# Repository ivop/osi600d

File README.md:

# Ohio Scientific 600D Remake

### Remake of the Ohio Scientific 600D PCB

* The new [schematics](doc/osi600d-schematic.pdf) are based on the original schematics, but with all [errors](doc/errors.txt) fixed.
* The PCB is mostly identical to the original, but with added silkscreen, and jumpers instead of trace cuts.
* In theory, you can build it solely with the [BOM](doc/osi600d-bom.pdf) and the new silkscreen, but the original Assembly Instructions still apply 100%.
* PCB uses Cherry MX key switches.
* 4-pin or 5-pin headers for USB-C or Micro USB breakout boards for power supply (e.g. Raspberry Pi 3A PS).
* Use [ramtest2114](https://github.com/ivop/ramtest2114) to test RAM chips acquired from Ali.

Can be paired with the [Ohio Scientific 610B Floppy Controller and Memory Expansion](https://github.com/ivop/osi610b).

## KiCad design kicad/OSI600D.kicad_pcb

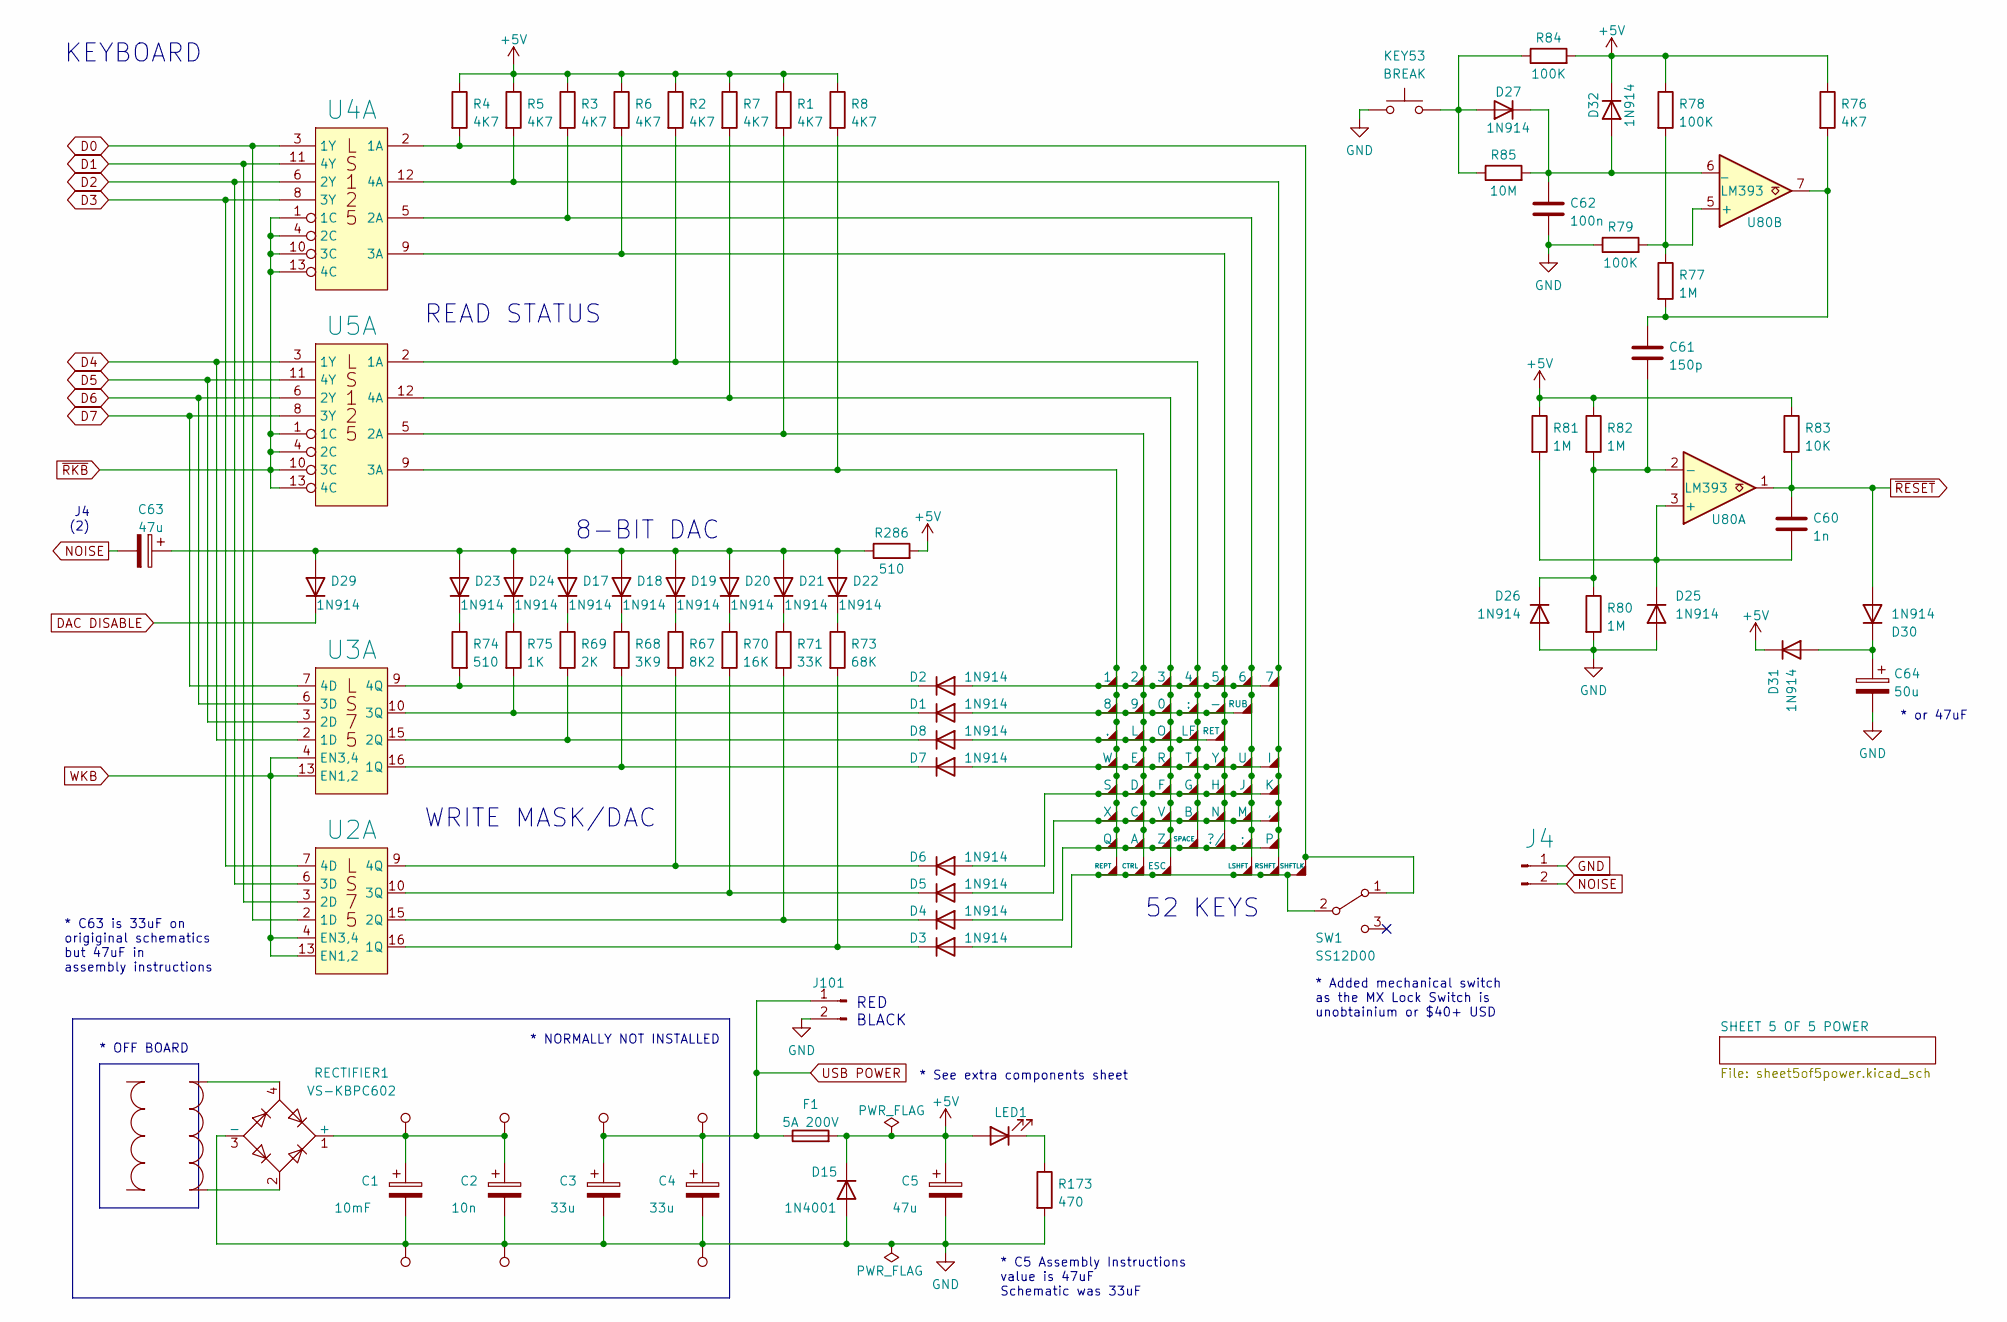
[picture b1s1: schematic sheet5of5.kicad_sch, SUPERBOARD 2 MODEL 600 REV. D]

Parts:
C1: 10mF; C_Radial_D10.0mm_H16.0mm_P5.00mm
C2: 10n; CP_Axial_L10.0mm_D4.5mm_P15.00mm_Horizontal
C3, C4: 33u; CP_Axial_L10.0mm_D4.5mm_P15.00mm_Horizontal
C5: 47u; CP_Axial_L10.0mm_D4.5mm_P15.00mm_Horizontal
C60: 1n; C_Disc_D7.5mm_W2.5mm_P7.50mm
C61: 150p; C_Disc_D7.5mm_W2.5mm_P7.50mm
C62: 100n; C_Disc_D7.5mm_W2.5mm_P7.50mm
C63: 47u; CP_Axial_L11.0mm_D5.0mm_P18.00mm_Horizontal
C64: 50u; CP_Axial_L11.0mm_D5.0mm_P18.00mm_Horizontal
D1, D2, D3, D4, D5, D6, D7, D8, D17, D18, D19, D20, D21, D22, D23, D24, D25, D26, D27, D29, D30, D31, D32: 1N914; D_DO-35_SOD27_P10.16mm_Horizontal
D15: 1N4001; D_DO-41_SOD81_P12.70mm_Horizontal
F1: 5A 200V; Fuse Holder
J4, J101: Conn_01x02_Male; Molex_KK-396_A-41791-0002_1x02_P3.96mm_Vertical
KEY1: 1; SW_Cherry_MX_PCB_1.00u
KEY2: 8; SW_Cherry_MX_PCB_1.00u
KEY3: .; SW_Cherry_MX_PCB_1.00u
KEY4: W; SW_Cherry_MX_PCB_1.00u
KEY5: S; SW_Cherry_MX_PCB_1.00u
KEY6: X; SW_Cherry_MX_PCB_1.00u
KEY7: Q; SW_Cherry_MX_PCB_1.00u
KEY8: REPT; SW_Cherry_MX_PCB_1.00u
KEY9: 2; SW_Cherry_MX_PCB_1.00u
KEY10: 9; SW_Cherry_MX_PCB_1.00u
KEY11: L; SW_Cherry_MX_PCB_1.00u
KEY12: E; SW_Cherry_MX_PCB_1.00u
KEY13: D; SW_Cherry_MX_PCB_1.00u
KEY14: C; SW_Cherry_MX_PCB_1.00u
KEY15: A; SW_Cherry_MX_PCB_1.00u
KEY16: CTRL; SW_Cherry_MX_PCB_1.00u
KEY17: 3; SW_Cherry_MX_PCB_1.00u
KEY18: 0; SW_Cherry_MX_PCB_1.00u
KEY19: O; SW_Cherry_MX_PCB_1.00u
KEY20: R; SW_Cherry_MX_PCB_1.00u
KEY21: F; SW_Cherry_MX_PCB_1.00u
KEY22: V; SW_Cherry_MX_PCB_1.00u
KEY23: Z; SW_Cherry_MX_PCB_1.00u
KEY24: ESC; SW_Cherry_MX_PCB_1.00u
KEY25: 4; SW_Cherry_MX_PCB_1.00u
KEY26: :; SW_Cherry_MX_PCB_1.00u
KEY27: LF; SW_Cherry_MX_PCB_1.00u
KEY28: T; SW_Cherry_MX_PCB_1.00u
KEY29: G; SW_Cherry_MX_PCB_1.00u
KEY30: B; SW_Cherry_MX_PCB_1.00u
KEY31: SPACE; SW_Cherry_MX_PCB_1.00u
KEY32: 5; SW_Cherry_MX_PCB_1.00u
KEY33: -; SW_Cherry_MX_PCB_1.00u
KEY34: RET; SW_Cherry_MX_PCB_1.50u
KEY35: Y; SW_Cherry_MX_PCB_1.00u
KEY36: H; SW_Cherry_MX_PCB_1.00u
KEY37: N; SW_Cherry_MX_PCB_1.00u
KEY38: ?/; SW_Cherry_MX_PCB_1.00u
KEY39: 6; SW_Cherry_MX_PCB_1.00u
KEY40: RUB; SW_Cherry_MX_PCB_1.00u
KEY41: U; SW_Cherry_MX_PCB_1.00u
KEY42: J; SW_Cherry_MX_PCB_1.00u
KEY43: M; SW_Cherry_MX_PCB_1.00u
KEY44: ;; SW_Cherry_MX_PCB_1.00u
KEY45: LSHFT; SW_Cherry_MX_PCB_1.50u
KEY46: 7; SW_Cherry_MX_PCB_1.00u
KEY47: I; SW_Cherry_MX_PCB_1.00u
KEY48: K; SW_Cherry_MX_PCB_1.00u
KEY49: ,; SW_Cherry_MX_PCB_1.00u
KEY50: P; SW_Cherry_MX_PCB_1.00u
KEY51: RSHFT; SW_Cherry_MX_PCB_1.50u
KEY52: SHFTLK; SW_Cherry_MX_PCB_1.00u
KEY53: BREAK; SW_Cherry_MX_PCB_1.00u
LED1: LED; LED_D5.0mm
PIN8, PIN9, PIN10, PIN11, PIN12, PIN13, PIN14: JUMPER_PIN; PinHeader_1x01_P2.54mm_Vertical
R1, R2, R3, R4, R5, R6, R7, R8: 4K7; R_Axial_DIN0207_L6.3mm_D2.5mm_P2.54mm_Vertical
R67: 8K2; R_Axial_DIN0207_L6.3mm_D2.5mm_P2.54mm_Vertical
R68: 3K9; R_Axial_DIN0207_L6.3mm_D2.5mm_P2.54mm_Vertical
R69: 2K; R_Axial_DIN0207_L6.3mm_D2.5mm_P2.54mm_Vertical
R70: 16K; R_Axial_DIN0207_L6.3mm_D2.5mm_P2.54mm_Vertical
R71: 33K; R_Axial_DIN0207_L6.3mm_D2.5mm_P2.54mm_Vertical
R73: 68K; R_Axial_DIN0207_L6.3mm_D2.5mm_P2.54mm_Vertical
R74: 510; R_Axial_DIN0207_L6.3mm_D2.5mm_P2.54mm_Vertical
R75: 1K; R_Axial_DIN0207_L6.3mm_D2.5mm_P2.54mm_Vertical
R76: 4K7; R_Axial_DIN0207_500mils_Horizontal
R77, R80, R81, R82: 1M; R_Axial_DIN0207_500mils_Horizontal
R78, R79, R84: 100K; R_Axial_DIN0207_500mils_Horizontal
R83: 10K; R_Axial_DIN0207_500mils_Horizontal
R85: 10M; R_Axial_DIN0207_500mils_Horizontal
R173: 470; R_Axial_DIN0207_L6.3mm_D2.5mm_P2.54mm_Vertical
R286: 510; R_Axial_DIN0207_500mils_Horizontal
RECTIFIER1: VS-KBPC602; Diode_Bridge_Vishay_KBPC6
SW1: SS12D00
TRANSFORMER1: TRANSFORMER_(OFF_BOARD); Molex_KK-396_A-41791-0002_1x02_P3.96mm_Vertical
U2, U3: LS75; DIP-16_W7.62mm_Socket_LongPads
U4, U5: LS125; DIP-14_W7.62mm_Socket_LongPads
U80: LM393; DIP-8_W7.62mm_Socket_LongPads

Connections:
+5V: C5.1, D15.1 (K), D31.1 (K), D32.1 (K), F1.2, LED1.2 (A), R1.1, R2.1, R3.1, R4.1, R5.1, R6.1, R7.1, R8.1, R76.1, R78.1, R81.1, R82.1, R83.1, R84.2, R286.2; also elsewhere on the board
D0: U2.2 (1D), U4.3 (1Y); also elsewhere on the board
D1: U2.3 (2D), U4.11 (4Y); also elsewhere on the board
D2: U2.6 (3D), U4.6 (2Y); also elsewhere on the board
D3: U2.7 (4D), U4.8 (3Y); also elsewhere on the board
D4: U3.2 (1D), U5.3 (1Y); also elsewhere on the board
D5: U3.3 (2D), U5.11 (4Y); also elsewhere on the board
D6: U3.6 (3D), U5.6 (2Y); also elsewhere on the board
D7: U3.7 (4D), U5.8 (3Y); also elsewhere on the board
DAC DISABLE: D29.1 (K); also elsewhere on the board
GND: C1.2, C2.2, C3.2, C4.2, C5.2, C62.2, C64.2, D15.2 (A), D25.2 (A), D26.2 (A), J4.1, J101.2, KEY53.2, PIN9.1, PIN11.1, PIN14.1, R79.1, R80.2, R173.2, RECTIFIER1.3 (-); also elsewhere on the board
NOISE: C63.2, J4.2
unnamed: C1.1, C2.1, PIN8.1, PIN10.1, RECTIFIER1.1 (+)
unnamed: C60.2, D25.1 (K), R81.2, U80.3 (+)
unnamed: C61.1, R76.2, R77.2, U80.7
unnamed: C61.2, D26.1 (K), R80.1, R82.2, U80.2 (-)
unnamed: C62.1, D27.1 (K), D32.2 (A), R85.2, U80.6 (_)
unnamed: C63.1, D17.2 (A), D18.2 (A), D19.2 (A), D20.2 (A), D21.2 (A), D22.2 (A), D23.2 (A), D24.2 (A), D29.2 (A), R286.1
unnamed: C64.1, D30.1 (K), D31.2 (A)
unnamed: D1.1 (K), R75.2, U3.10 (3Q), U3.14 (~2Q)
unnamed: D1.2 (A), KEY2.1, KEY10.1, KEY18.1, KEY26.1, KEY33.1, KEY40.1
unnamed: D2.1 (K), R74.2, U3.9 (4Q)
unnamed: D2.2 (A), KEY1.1, KEY9.1, KEY17.1, KEY25.1, KEY32.1, KEY39.1, KEY46.1
unnamed: D3.1 (K), R73.2, U2.16 (1Q)
unnamed: D3.2 (A), KEY8.1, KEY16.1, KEY24.1, KEY45.1, KEY51.1, KEY52.1, SW1.2 (B)
unnamed: D4.1 (K), R71.2, U2.15 (2Q)
unnamed: D4.2 (A), KEY7.1, KEY15.1, KEY23.1, KEY31.1, KEY38.1, KEY44.1, KEY50.1
unnamed: D5.1 (K), R70.2, U2.10 (3Q)
unnamed: D5.2 (A), KEY6.1, KEY14.1, KEY22.1, KEY30.1, KEY37.1, KEY43.1, KEY49.1
unnamed: D6.1 (K), R67.2, U2.9 (4Q)
unnamed: D6.2 (A), KEY5.1, KEY13.1, KEY21.1, KEY29.1, KEY36.1, KEY42.1, KEY48.1
unnamed: D7.1 (K), R68.2, U3.16 (1Q)
unnamed: D7.2 (A), KEY4.1, KEY12.1, KEY20.1, KEY28.1, KEY35.1, KEY41.1, KEY47.1
unnamed: D8.1 (K), R69.2, U3.15 (2Q)
unnamed: D8.2 (A), KEY3.1, KEY11.1, KEY19.1, KEY27.1, KEY34.1
unnamed: D17.1 (K), R69.1
unnamed: D18.1 (K), R68.1
unnamed: D19.1 (K), R67.1
unnamed: D20.1 (K), R70.1
unnamed: D21.1 (K), R71.1
unnamed: D22.1 (K), R73.1
unnamed: D23.1 (K), R74.1
unnamed: D24.1 (K), R75.1
unnamed: D27.2 (A), KEY53.1, R84.1, R85.1
unnamed: KEY1.2, KEY2.2, KEY3.2, KEY4.2, KEY5.2, KEY6.2, KEY7.2, KEY8.2, R8.2, U5.9 (3A)
unnamed: KEY9.2, KEY10.2, KEY11.2, KEY12.2, KEY13.2, KEY14.2, KEY15.2, KEY16.2, R1.2, U5.5 (2A)
unnamed: KEY17.2, KEY18.2, KEY19.2, KEY20.2, KEY21.2, KEY22.2, KEY23.2, KEY24.2, R7.2, U5.12 (4A)
unnamed: KEY25.2, KEY26.2, KEY27.2, KEY28.2, KEY29.2, KEY30.2, KEY31.2, R2.2, U5.2 (1A)
unnamed: KEY32.2, KEY33.2, KEY34.2, KEY35.2, KEY36.2, KEY37.2, KEY38.2, R6.2, U4.9 (3A)
unnamed: KEY39.2, KEY40.2, KEY41.2, KEY42.2, KEY43.2, KEY44.2, KEY45.2, R3.2, U4.5 (2A)
unnamed: KEY46.2, KEY47.2, KEY48.2, KEY49.2, KEY50.2, KEY51.2, R5.2, U4.12 (4A)
unnamed: KEY52.2, R4.2, SW1.1 (A), U4.2 (1A)
unnamed: LED1.1 (K), R173.1
unnamed: R77.1, R78.2, R79.2, U80.5 (+)
unnamed 171: RECTIFIER1.2, TRANSFORMER1.2; also elsewhere on the board
unnamed: RECTIFIER1.4, TRANSFORMER1.1
USB POWER: C3.1, C4.1, F1.1, J101.1, PIN12.1, PIN13.1; also elsewhere on the board
WKB: U2.4 (EN3,4), U2.13 (EN1,2), U3.4 (EN3,4), U3.13 (EN1,2); also elsewhere on the board
~RESET: C60.1, D30.2 (A), R83.2, U80.1; also elsewhere on the board
~RKB: U4.1 (1C), U4.4 (2C), U4.10 (3C), U4.13 (4C), U5.1 (1C), U5.4 (2C), U5.10 (3C), U5.13 (4C); also elsewhere on the board

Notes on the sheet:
52 KEYS
* OFF BOARD
* NORMALLY NOT INSTALLED
KEYBOARD
* C5 Assembly Instructions value is 47uF Schematic was 33uF
READ STATUS
* Added mechanical switch as the MX Lock Switch is unobtainium or $40+ USD
WRITE MASK/DAC
* or 47uF
* C63 is 33uF on origiginal schematics but 47uF in assembly instructions
* See extra components sheet
J4 (2)
8-BIT DAC
RED BLACK

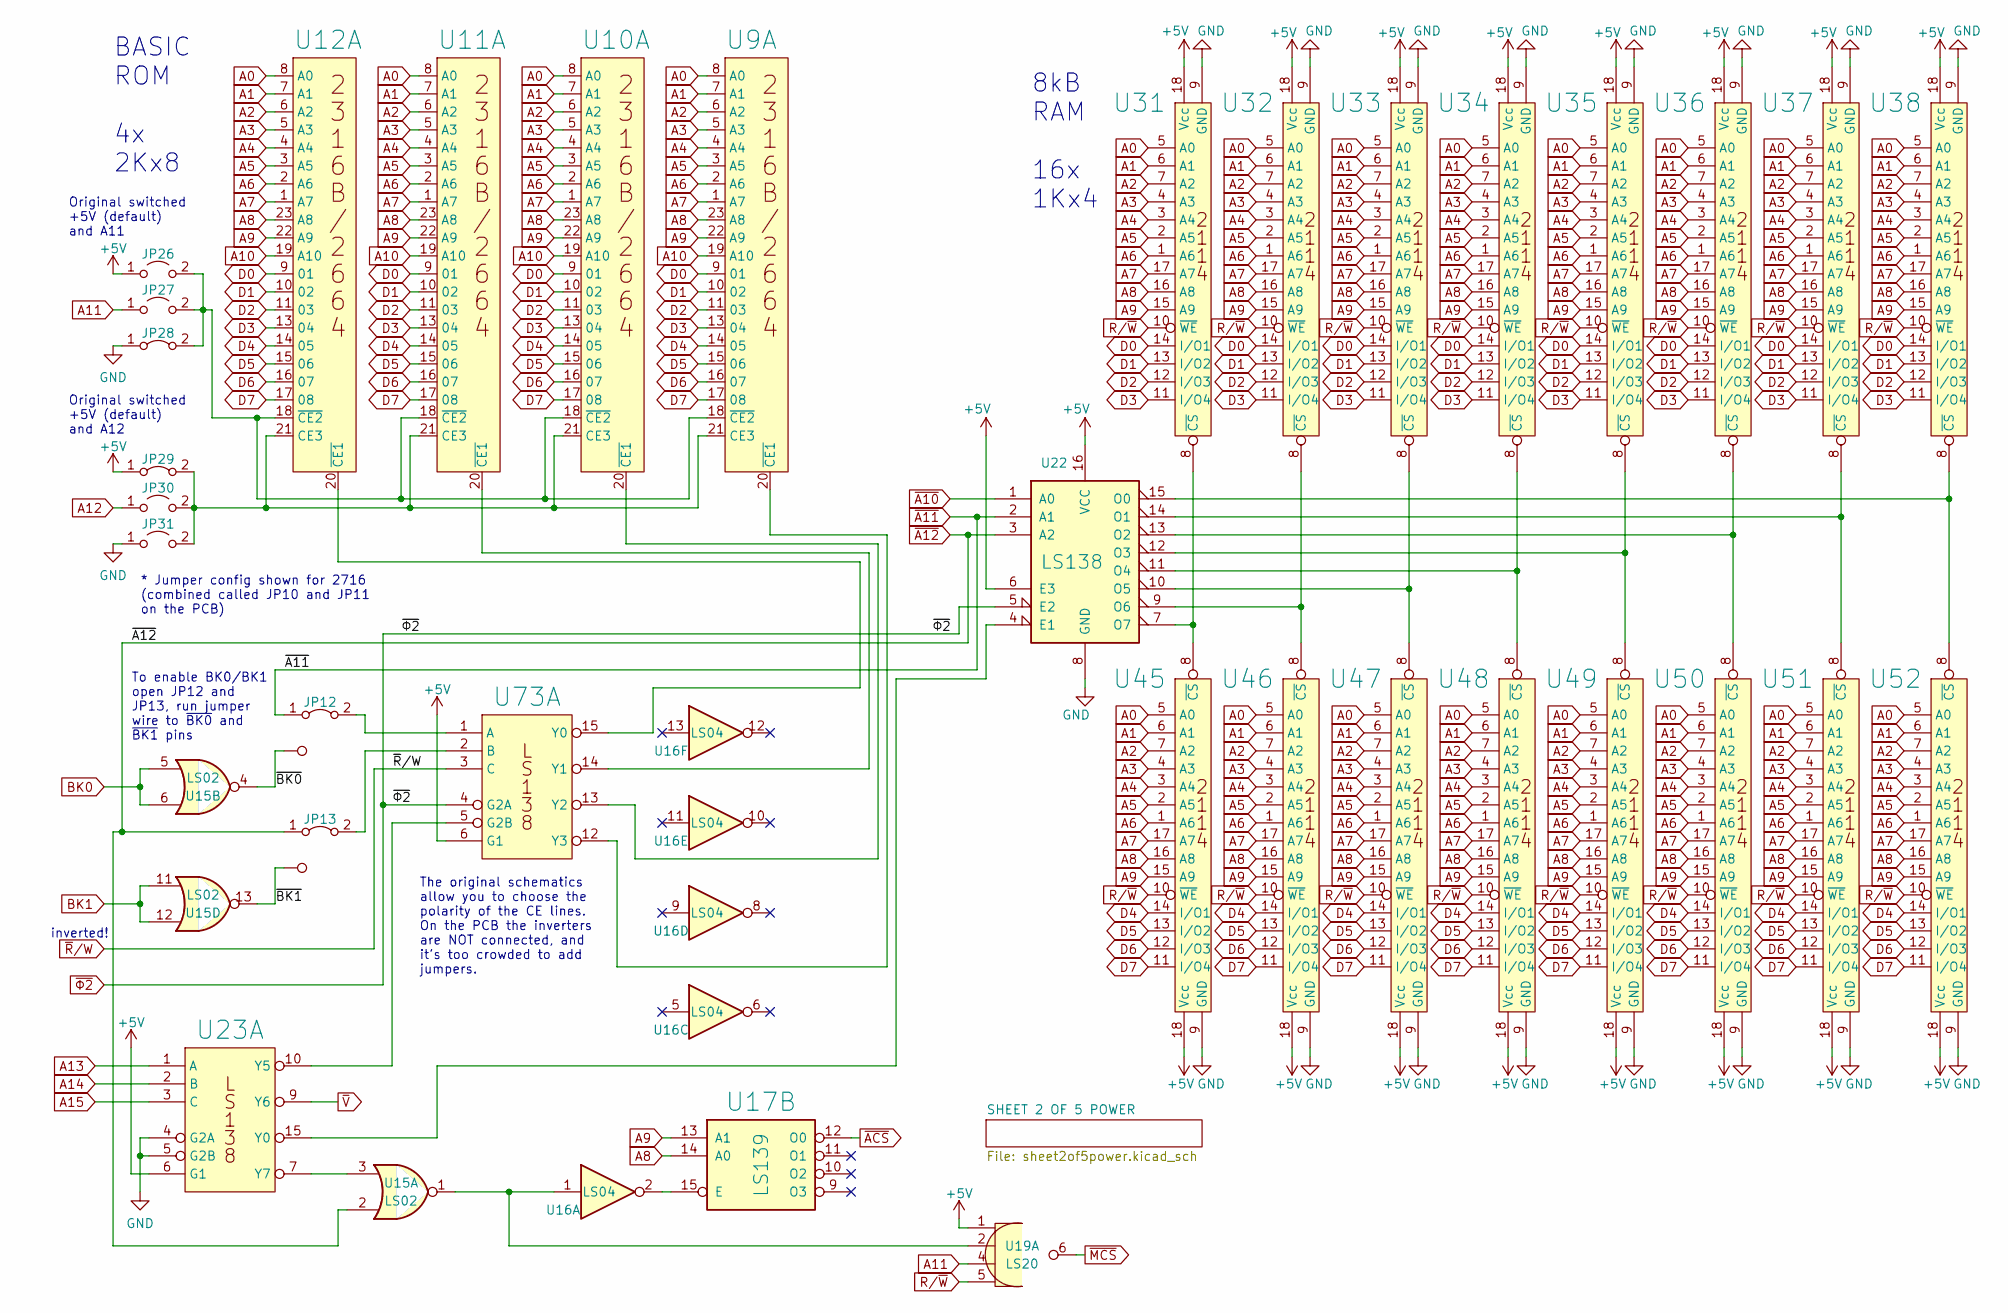
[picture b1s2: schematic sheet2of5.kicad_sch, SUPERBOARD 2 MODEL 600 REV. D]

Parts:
JP12, JP13, JP28, JP29: Jumper_2_Bridged; Closed_PinHeader_1x02_P2.54mm_Vertical
JP26, JP27, JP30, JP31: Jumper_2_Open; PinHeader_1x02_P2.54mm_Vertical
PIN17, PIN18: JUMPER_PIN; PinHeader_1x01_P2.54mm_Vertical
U9: BASIC 1; DIP-24_W15.24mm_Socket_LongPads
U10: BASIC 2; DIP-24_W15.24mm_Socket_LongPads
U11: BASIC 3; DIP-24_W15.24mm_Socket_LongPads
U12: BASIC 4; DIP-24_W15.24mm_Socket_LongPads
U15: LS02; DIP-14_W7.62mm_Socket_LongPads
U16: LS04; DIP-14_W7.62mm_Socket_LongPads
U17: LS139; DIP-16_W7.62mm_Socket_LongPads
U19: LS20; DIP-14_W7.62mm_Socket_LongPads
U22, U23, U73: LS138; DIP-16_W7.62mm_Socket_LongPads
U31, U32, U33, U34, U35, U36, U37, U38: 2114 CS BOTTOM; DIP-18_W7.62mm_Socket_LongPads
U45, U46, U47, U48, U49, U50, U51, U52: 2114 CS TOP; DIP-18_W7.62mm_Socket_LongPads

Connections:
+5V: JP26.1 (A), JP29.1 (A), U19.1 (1A), U22.6 (E3), U22.16 (VCC), U23.6 (G1), U31.18 (Vcc), U32.18 (Vcc), U33.18 (Vcc), U34.18 (Vcc), U35.18 (Vcc), U36.18 (Vcc), U37.18 (Vcc), U38.18 (Vcc), U45.18 (Vcc), U46.18 (Vcc), U47.18 (Vcc), U48.18 (Vcc), U49.18 (Vcc), U50.18 (Vcc), U51.18 (Vcc), U52.18 (Vcc), U73.6 (G1); also elsewhere on the board
/SHEET 2 OF 5/~BK0: PIN17.1, U15.4
/SHEET 2 OF 5/~BK1: PIN18.1, U15.13
A0: U9.8 (A0), U10.8 (A0), U11.8 (A0), U12.8 (A0), U31.5 (A0), U32.5 (A0), U33.5 (A0), U34.5 (A0), U35.5 (A0), U36.5 (A0), U37.5 (A0), U38.5 (A0), U45.5 (A0), U46.5 (A0), U47.5 (A0), U48.5 (A0), U49.5 (A0), U50.5 (A0), U51.5 (A0), U52.5 (A0); also elsewhere on the board
A1: U9.7 (A1), U10.7 (A1), U11.7 (A1), U12.7 (A1), U31.6 (A1), U32.6 (A1), U33.6 (A1), U34.6 (A1), U35.6 (A1), U36.6 (A1), U37.6 (A1), U38.6 (A1), U45.6 (A1), U46.6 (A1), U47.6 (A1), U48.6 (A1), U49.6 (A1), U50.6 (A1), U51.6 (A1), U52.6 (A1); also elsewhere on the board
A2: U9.6 (A2), U10.6 (A2), U11.6 (A2), U12.6 (A2), U31.7 (A2), U32.7 (A2), U33.7 (A2), U34.7 (A2), U35.7 (A2), U36.7 (A2), U37.7 (A2), U38.7 (A2), U45.7 (A2), U46.7 (A2), U47.7 (A2), U48.7 (A2), U49.7 (A2), U50.7 (A2), U51.7 (A2), U52.7 (A2); also elsewhere on the board
A3: U9.5 (A3), U10.5 (A3), U11.5 (A3), U12.5 (A3), U31.4 (A3), U32.4 (A3), U33.4 (A3), U34.4 (A3), U35.4 (A3), U36.4 (A3), U37.4 (A3), U38.4 (A3), U45.4 (A3), U46.4 (A3), U47.4 (A3), U48.4 (A3), U49.4 (A3), U50.4 (A3), U51.4 (A3), U52.4 (A3); also elsewhere on the board
A4: U9.4 (A4), U10.4 (A4), U11.4 (A4), U12.4 (A4), U31.3 (A4), U32.3 (A4), U33.3 (A4), U34.3 (A4), U35.3 (A4), U36.3 (A4), U37.3 (A4), U38.3 (A4), U45.3 (A4), U46.3 (A4), U47.3 (A4), U48.3 (A4), U49.3 (A4), U50.3 (A4), U51.3 (A4), U52.3 (A4); also elsewhere on the board
A5: U9.3 (A5), U10.3 (A5), U11.3 (A5), U12.3 (A5), U31.2 (A5), U32.2 (A5), U33.2 (A5), U34.2 (A5), U35.2 (A5), U36.2 (A5), U37.2 (A5), U38.2 (A5), U45.2 (A5), U46.2 (A5), U47.2 (A5), U48.2 (A5), U49.2 (A5), U50.2 (A5), U51.2 (A5), U52.2 (A5); also elsewhere on the board
A6: U9.2 (A6), U10.2 (A6), U11.2 (A6), U12.2 (A6), U31.1 (A6), U32.1 (A6), U33.1 (A6), U34.1 (A6), U35.1 (A6), U36.1 (A6), U37.1 (A6), U38.1 (A6), U45.1 (A6), U46.1 (A6), U47.1 (A6), U48.1 (A6), U49.1 (A6), U50.1 (A6), U51.1 (A6), U52.1 (A6); also elsewhere on the board
A7: U9.1 (A7), U10.1 (A7), U11.1 (A7), U12.1 (A7), U31.17 (A7), U32.17 (A7), U33.17 (A7), U34.17 (A7), U35.17 (A7), U36.17 (A7), U37.17 (A7), U38.17 (A7), U45.17 (A7), U46.17 (A7), U47.17 (A7), U48.17 (A7), U49.17 (A7), U50.17 (A7), U51.17 (A7), U52.17 (A7); also elsewhere on the board
A8: U9.23 (A8), U10.23 (A8), U11.23 (A8), U12.23 (A8), U17.14 (A0), U31.16 (A8), U32.16 (A8), U33.16 (A8), U34.16 (A8), U35.16 (A8), U36.16 (A8), U37.16 (A8), U38.16 (A8), U45.16 (A8), U46.16 (A8), U47.16 (A8), U48.16 (A8), U49.16 (A8), U50.16 (A8), U51.16 (A8), U52.16 (A8); also elsewhere on the board
A9: U9.22 (A9), U10.22 (A9), U11.22 (A9), U12.22 (A9), U17.13 (A1), U31.15 (A9), U32.15 (A9), U33.15 (A9), U34.15 (A9), U35.15 (A9), U36.15 (A9), U37.15 (A9), U38.15 (A9), U45.15 (A9), U46.15 (A9), U47.15 (A9), U48.15 (A9), U49.15 (A9), U50.15 (A9), U51.15 (A9), U52.15 (A9); also elsewhere on the board
A10: U9.19 (A10), U10.19 (A10), U11.19 (A10), U12.19 (A10); also elsewhere on the board
A11: JP27.1 (A), U19.4 (1C); also elsewhere on the board
A12: JP30.1 (A); also elsewhere on the board
A13: U23.1 (A); also elsewhere on the board
A14: U23.2 (B); also elsewhere on the board
A15: U23.3 (C); also elsewhere on the board
BK0: U15.5, U15.6; also elsewhere on the board
BK1: U15.11, U15.12; also elsewhere on the board
D0: U9.9 (01), U10.9 (01), U11.9 (01), U12.9 (01), U31.14 (I/O1), U32.14 (I/O1), U33.14 (I/O1), U34.14 (I/O1), U35.14 (I/O1), U36.14 (I/O1), U37.14 (I/O1), U38.14 (I/O1); also elsewhere on the board
D1: U9.10 (02), U10.10 (02), U11.10 (02), U12.10 (02), U31.13 (I/O2), U32.13 (I/O2), U33.13 (I/O2), U34.13 (I/O2), U35.13 (I/O2), U36.13 (I/O2), U37.13 (I/O2), U38.13 (I/O2); also elsewhere on the board
D2: U9.11 (03), U10.11 (03), U11.11 (03), U12.11 (03), U31.12 (I/O3), U32.12 (I/O3), U33.12 (I/O3), U34.12 (I/O3), U35.12 (I/O3), U36.12 (I/O3), U37.12 (I/O3), U38.12 (I/O3); also elsewhere on the board
D3: U9.13 (04), U10.13 (04), U11.13 (04), U12.13 (04), U31.11 (I/O4), U32.11 (I/O4), U33.11 (I/O4), U34.11 (I/O4), U35.11 (I/O4), U36.11 (I/O4), U37.11 (I/O4), U38.11 (I/O4); also elsewhere on the board
D4: U9.14 (05), U10.14 (05), U11.14 (05), U12.14 (05), U45.14 (I/O1), U46.14 (I/O1), U47.14 (I/O1), U48.14 (I/O1), U49.14 (I/O1), U50.14 (I/O1), U51.14 (I/O1), U52.14 (I/O1); also elsewhere on the board
D5: U9.15 (06), U10.15 (06), U11.15 (06), U12.15 (06), U45.13 (I/O2), U46.13 (I/O2), U47.13 (I/O2), U48.13 (I/O2), U49.13 (I/O2), U50.13 (I/O2), U51.13 (I/O2), U52.13 (I/O2); also elsewhere on the board
D6: U9.16 (07), U10.16 (07), U11.16 (07), U12.16 (07), U45.12 (I/O3), U46.12 (I/O3), U47.12 (I/O3), U48.12 (I/O3), U49.12 (I/O3), U50.12 (I/O3), U51.12 (I/O3), U52.12 (I/O3); also elsewhere on the board
D7: U9.17 (08), U10.17 (08), U11.17 (08), U12.17 (08), U45.11 (I/O4), U46.11 (I/O4), U47.11 (I/O4), U48.11 (I/O4), U49.11 (I/O4), U50.11 (I/O4), U51.11 (I/O4), U52.11 (I/O4); also elsewhere on the board
GND: JP28.1 (A), JP31.1 (A), U22.8 (GND), U23.4 (G2A), U23.5 (G2B), U31.9 (GND), U32.9 (GND), U33.9 (GND), U34.9 (GND), U35.9 (GND), U36.9 (GND), U37.9 (GND), U38.9 (GND), U45.9 (GND), U46.9 (GND), U47.9 (GND), U48.9 (GND), U49.9 (GND), U50.9 (GND), U51.9 (GND), U52.9 (GND); also elsewhere on the board
unnamed: JP12.2 (B), U73.1 (A)
unnamed: JP13.2 (B), U73.2 (B)
unnamed: JP26.2 (B), JP27.2 (B), JP28.2 (B), U9.18 (~CE2), U10.18 (~CE2), U11.18 (~CE2), U12.18 (~CE2)
unnamed: JP29.2 (B), JP30.2 (B), JP31.2 (B), U9.21 (CE3), U10.21 (CE3), U11.21 (CE3), U12.21 (CE3)
unnamed: U10.20 (~CE1), U73.13 (Y2)
unnamed: U11.20 (~CE1), U73.14 (Y1)
unnamed: U12.20 (~CE1), U73.15 (Y0)
unnamed: U15.1, U16.1, U19.2 (1B)
unnamed: U15.3, U23.7 (Y7)
unnamed: U16.2, U17.15 (E)
unnamed: U22.4 (E1), U23.15 (Y0)
unnamed: U22.7 (O7), U31.8 (~CS), U45.8 (~CS)
unnamed: U22.9 (O6), U32.8 (~CS), U46.8 (~CS)
unnamed: U22.10 (O5), U33.8 (~CS), U47.8 (~CS)
unnamed: U22.11 (O4), U34.8 (~CS), U48.8 (~CS)
unnamed: U22.12 (O3), U35.8 (~CS), U49.8 (~CS)
unnamed: U22.13 (O2), U36.8 (~CS), U50.8 (~CS)
unnamed: U22.14 (O1), U37.8 (~CS), U51.8 (~CS)
unnamed: U22.15 (O0), U38.8 (~CS), U52.8 (~CS)
unnamed: U23.10 (Y5), U73.5 (G2B)
unnamed: U9.20 (~CE1), U73.12 (Y3)
R/~W: U19.5 (1D), U31.10 (~WE), U32.10 (~WE), U33.10 (~WE), U34.10 (~WE), U35.10 (~WE), U36.10 (~WE), U37.10 (~WE), U38.10 (~WE), U45.10 (~WE), U46.10 (~WE), U47.10 (~WE), U48.10 (~WE), U49.10 (~WE), U50.10 (~WE), U51.10 (~WE), U52.10 (~WE); also elsewhere on the board
~A10: U22.1 (A0); also elsewhere on the board
~A11: JP12.1 (A), U22.2 (A1); also elsewhere on the board
~A12: JP13.1 (A), U15.2, U22.3 (A2); also elsewhere on the board
~ACS: U17.12 (O0); also elsewhere on the board
~MCS: U19.6 (1Y); also elsewhere on the board
~R/W: U73.3 (C); also elsewhere on the board
~V: U23.9 (Y6); also elsewhere on the board
~Φ2: U22.5 (E2), U73.4 (G2A); also elsewhere on the board

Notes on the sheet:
To enable BK0/BK1 open JP12 and JP13, run jumper wire to ~{BK0} and ~{BK1} pins
8kB RAM 16x 1Kx4
The original schematics allow you to choose the polarity of the CE lines. On the PCB the inverters are NOT connected, and it's too crowded to add jumpers.
BASIC ROM 4x 2Kx8
inverted!
Original switched +5V (default) and A12
* Jumper config shown for 2716 (combined called JP10 and JP11 on the PCB)
Original switched +5V (default) and A11

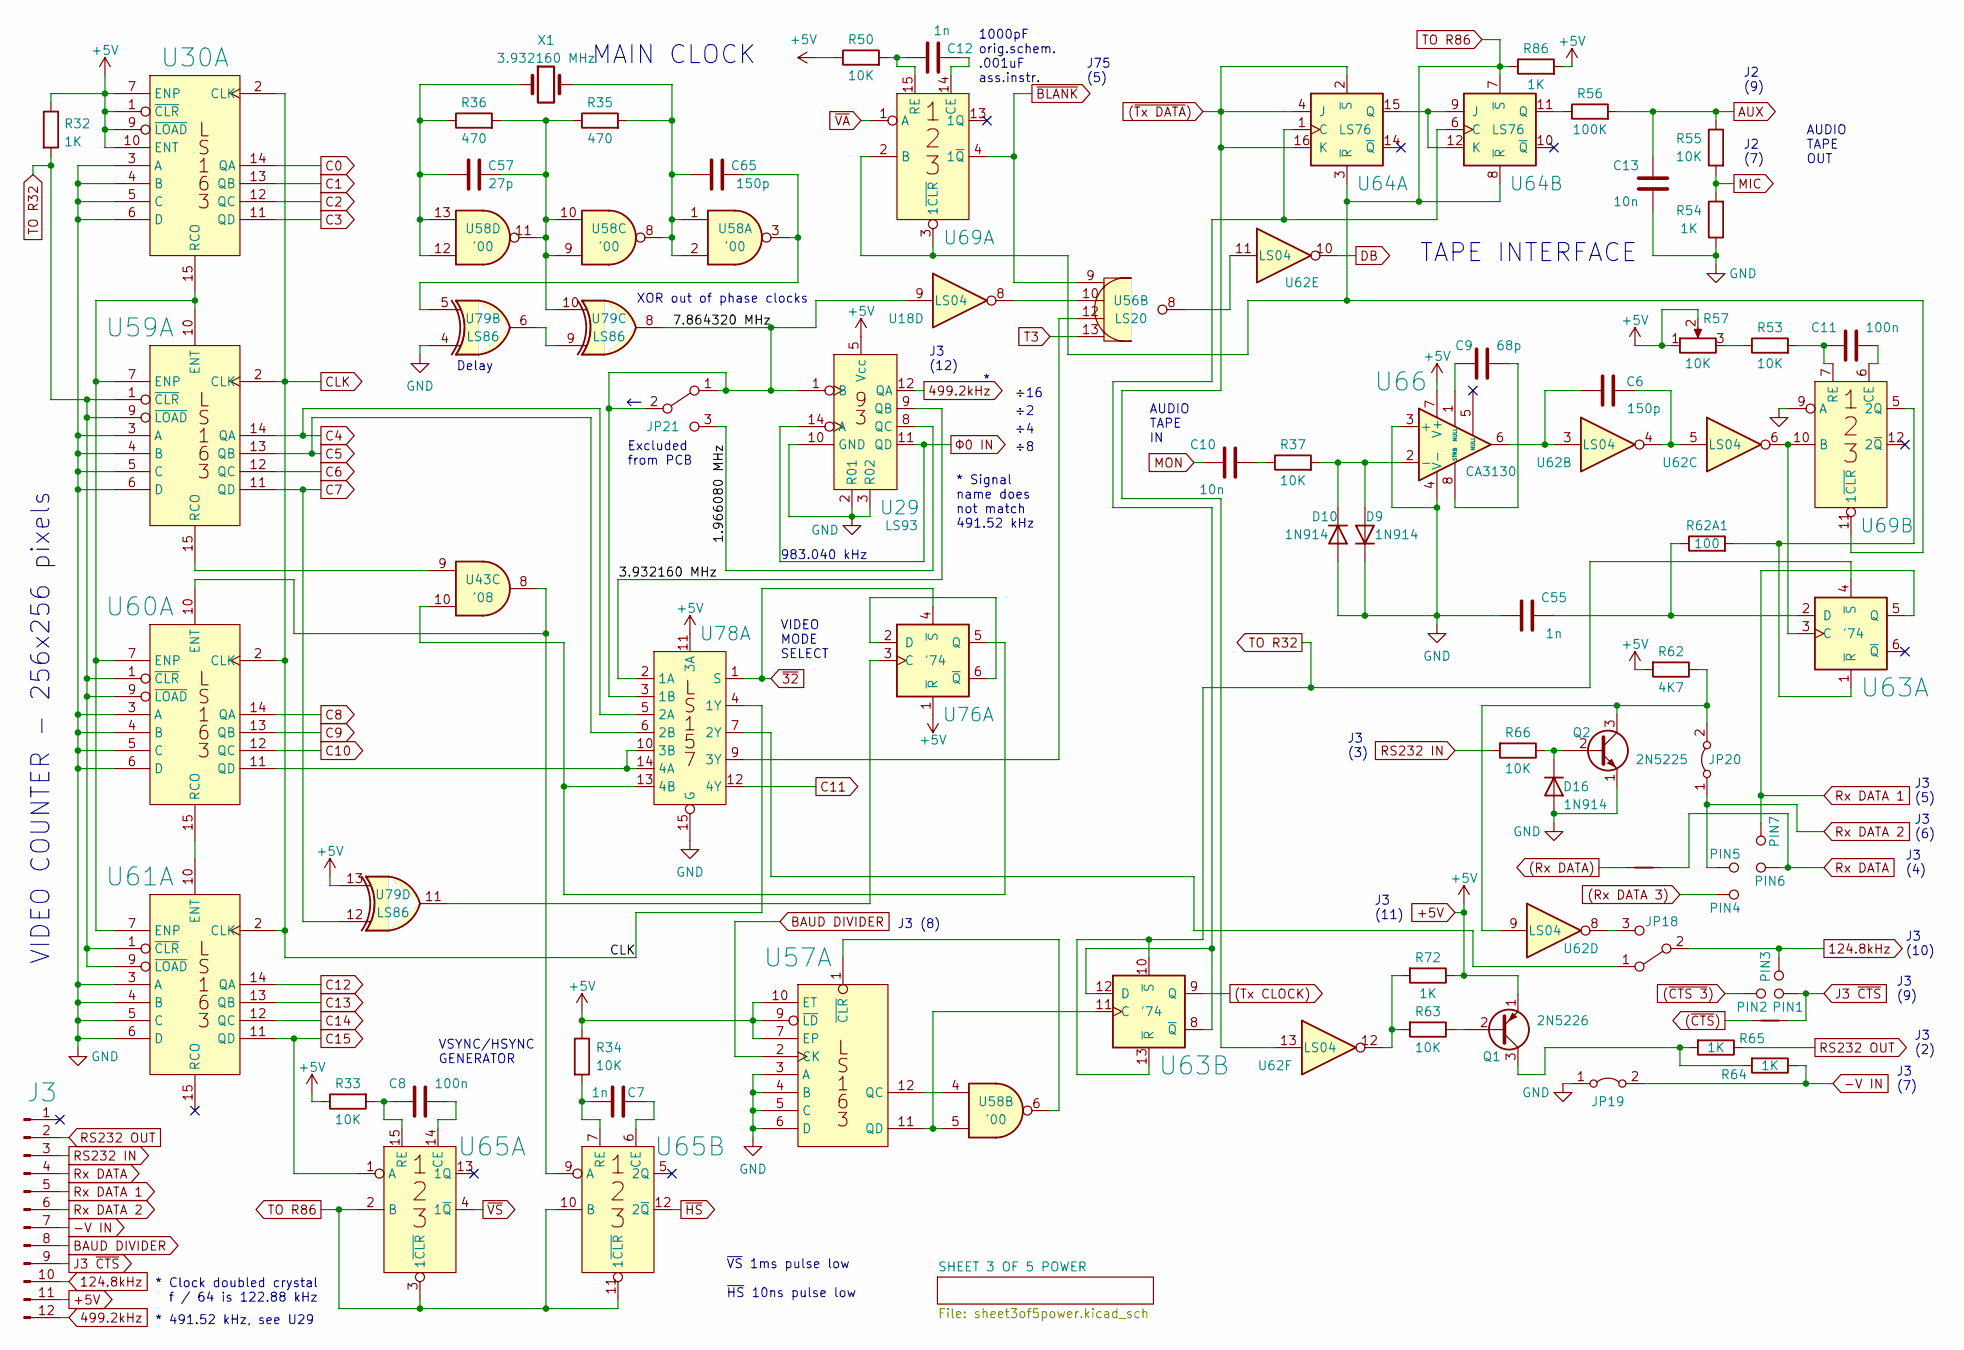
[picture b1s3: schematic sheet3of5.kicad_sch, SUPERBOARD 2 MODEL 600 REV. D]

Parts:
C6, C65: 150p; C_Disc_D7.5mm_W2.5mm_P7.50mm
C7, C12, C55: 1n; C_Disc_D7.5mm_W2.5mm_P7.50mm
C8: 100n; C_Disc_D5.1mm_W3.2mm_P5.00mm
C9: 68p; C_Disc_D7.5mm_W2.5mm_P7.50mm
C10, C13: 10n; C_Disc_D7.5mm_W2.5mm_P7.50mm
C11: 100n; C_Disc_D7.5mm_W2.5mm_P7.50mm
C57: 27p; C_Disc_D4.3mm_W1.9mm_P5.00mm
D9, D10: 1N914; D_DO-35_SOD27_P10.16mm_Horizontal
D16: 1N914; D_DO-35_SOD27_P5.08mm_Vertical_KathodeUp
J3: Conn_01x12_Male; Molex_KK-396_A-41791-0012_1x12_P3.96mm_Vertical
JP18, JP21: JUMPER; PinHeader_1x03_P2.54mm_Vertical
JP19, JP20: Jumper_2_Bridged; Closed_PinHeader_1x02_P2.54mm_Vertical
NT1, NT2: NetTie_2; NetTie-2_SMD_Pad0.5mm
PIN1, PIN2, PIN3, PIN4, PIN5, PIN6, PIN7: JUMPER_PIN; PinHeader_1x01_P2.54mm_Vertical
Q1: 2N5226; TO-92_Inline_Wide
Q2: 2N5225; TO-92_Inline_Wide
R32, R54, R72, R86: 1K; R_Axial_DIN0207_L6.3mm_D2.5mm_P2.54mm_Vertical
R33, R34, R50, R53, R55, R63, R66: 10K; R_Axial_DIN0207_L6.3mm_D2.5mm_P2.54mm_Vertical
R35, R36: 470; R_Axial_DIN0207_L6.3mm_D2.5mm_P2.54mm_Vertical
R37: 10K; R_Axial_DIN0207_500mils_Horizontal
R56: 100K; R_Axial_DIN0207_L6.3mm_D2.5mm_P2.54mm_Vertical
R57: 10K; Potentiometer_Bourns_3296W_Vertical
R62: 4K7; R_Axial_DIN0207_L6.3mm_D2.5mm_P2.54mm_Vertical
R62A1: 100; R_Axial_DIN0207_L6.3mm_D2.5mm_P2.54mm_Vertical
R64, R65: 1K; R_Axial_DIN0309_L9.0mm_D3.2mm_P20.32mm_Horizontal
U18, U62: LS04; DIP-14_W7.62mm_Socket_LongPads
U29: LS93; DIP-14_W7.62mm_Socket_LongPads
U30, U57, U59, U60, U61: LS163; DIP-16_W7.62mm_Socket_LongPads
U43: '08; DIP-14_W7.62mm_Socket_LongPads
U56: LS20; DIP-14_W7.62mm_Socket_LongPads
U58: '00; DIP-14_W7.62mm_Socket_LongPads
U63, U76: '74; DIP-14_W7.62mm_Socket_LongPads
U64: LS76; DIP-16_W7.62mm_Socket_LongPads
U65, U69: '123; DIP-16_W7.62mm_Socket_LongPads
U66: CA3130; DIP-8_W7.62mm_Socket_LongPads
U78: LS157; DIP-16_W7.62mm_Socket_LongPads
U79: LS86; DIP-14_W7.62mm_Socket_LongPads
X1: 3.932160 MHz; Crystal_HC49-U_Horizontal

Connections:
124.8kHz: J3.10, JP18.2, PIN3.1
499.2kHz: J3.12, U29.12 (QA)
(Rx DATA 3): PIN4.1; also elsewhere on the board
(Rx DATA): NT2.1; also elsewhere on the board
(Tx CLOCK): U63.9 (Q); also elsewhere on the board
(~CTS 3): PIN2.1; also elsewhere on the board
(~CTS): NT1.1; also elsewhere on the board
(~Tx DATA): U62.13, U64.2 (~S), U64.4 (J), U64.16 (K); also elsewhere on the board
+5V: J3.11, Q1.1 (E), R32.1, R33.1, R34.1, R50.1, R57.1, R57.2, R62.2, R72.1, R86.2, U29.5 (Vcc), U30.1 (~CLR), U30.7 (ENP), U30.9 (~LOAD), U30.10 (ENT), U57.7 (EP), U57.9 (~LD), U57.10 (ET), U66.7 (V+), U76.1 (~R), U78.11 (3A), U79.13; also elsewhere on the board
-V IN: J3.7, JP19.2 (B), R64.1
/SHEET 3 OF 5/1.966080 MHz: JP21.3, U29.8 (QC)
/SHEET 3 OF 5/3.932160 MHz: U29.9 (QB), U78.2 (1A)
/SHEET 3 OF 5/7.864320 MHz: JP21.1, JP21.2, U18.9, U29.1 (B), U78.3 (1B), U79.8
AUX: C13.2, R55.1, R56.2; also elsewhere on the board
BAUD DIVIDER: J3.8, U57.2 (CK)
C0: U30.14 (QA); also elsewhere on the board
C1: U30.13 (QB); also elsewhere on the board
C2: U30.12 (QC); also elsewhere on the board
C3: U30.11 (QD); also elsewhere on the board
C4: U59.14 (QA), U78.5 (2A); also elsewhere on the board
C5: U59.13 (QB), U78.6 (2B); also elsewhere on the board
C6: U59.12 (QC); also elsewhere on the board
C7: U59.11 (QD), U79.12; also elsewhere on the board
C8: U60.14 (QA); also elsewhere on the board
C9: U60.13 (QB); also elsewhere on the board
C10: U60.12 (QC); also elsewhere on the board
C11: U78.12 (4Y); also elsewhere on the board
C12: U61.14 (QA); also elsewhere on the board
C13: U61.13 (QB); also elsewhere on the board
C14: U61.12 (QC); also elsewhere on the board
C15: U61.11 (QD), U65.1 (A); also elsewhere on the board
CLK: U30.2 (CLK), U59.2 (CLK), U60.2 (CLK), U61.2 (CLK), U78.4 (1Y); also elsewhere on the board
DB: U62.10; also elsewhere on the board
GND: C13.1, C55.1, D9.1 (K), D10.2 (A), D16.2 (A), JP19.1 (A), Q2.1 (E), R54.1, U29.2 (R01), U29.3 (R02), U29.10 (GND), U30.3 (A), U30.4 (B), U30.5 (C), U30.6 (D), U57.3 (A), U57.4 (B), U57.5 (C), U57.6 (D), U59.3 (A), U59.4 (B), U59.5 (C), U59.6 (D), U60.3 (A), U60.4 (B), U60.5 (C), U60.6 (D), U61.3 (A), U61.4 (B), U61.5 (C), U61.6 (D), U66.3 (+), U66.4 (V-), U69.9 (A), U78.15 (G), U79.4; also elsewhere on the board
J3 ~CTS: J3.9, NT1.2, PIN1.1
MIC: R54.2, R55.2; also elsewhere on the board
MON: C10.1; also elsewhere on the board
unnamed: C6.1, U62.3, U66.6
unnamed: C6.2, U62.4, U62.5
unnamed: C7.1, R34.2, U65.7 (RE)
unnamed: C7.2, U65.6 (CE)
unnamed: C8.1, R33.2, U65.15 (RE)
unnamed: C8.2, U65.14 (CE)
unnamed: C9.1, U66.1 (NULL)
unnamed: C9.2, U66.8 (STRB)
unnamed: C10.2, R37.1
unnamed: C11.1, R53.2, U69.7 (RE)
unnamed: C11.2, U69.6 (CE)
unnamed: C12.1, R50.2, U69.15 (RE)
unnamed: C12.2, U69.14 (CE)
unnamed: C55.2, R62A1.1, U63.2 (D)
unnamed: C57.1, R36.1, U58.12, U58.13, X1.1
unnamed: C57.2, R35.1, R36.2, U58.9, U58.10, U58.11, U79.10
unnamed 106: C65.1, R35.2, U58.1, U58.2, U58.8, X1.2; also elsewhere on the board
unnamed: C65.2, U58.3, U79.5
unnamed: D9.2 (A), D10.1 (K), R37.2, U66.2 (-)
unnamed: D16.1 (K), Q2.2 (B), R66.1
unnamed: JP18.1, U78.7 (2Y)
unnamed: JP18.3, U62.8
unnamed: JP20.2 (B), Q2.3 (C), R62.1, U62.9
unnamed: Q1.2 (B), R63.1
unnamed: Q1.3 (C), R64.2, R65.2
unnamed: R53.1, R57.3
unnamed: R56.1, U64.11 (Q)
unnamed: R62A1.2, U63.1 (~R), U69.5 (2Q)
unnamed: R63.2, R72.2, U62.12
unnamed: U18.8, U56.10 (2B)
unnamed: U30.15 (RCO), U59.7 (ENP), U59.10 (ENT), U60.7 (ENP), U61.7 (ENP)
unnamed: U43.8, U60.10 (ENT), U65.9 (A)
unnamed: U43.9, U59.15 (RCO)
unnamed: U43.10, U76.5 (Q), U78.13 (4B)
unnamed: U56.8 (2Y), U62.11
unnamed: U56.12 (2C), U78.9 (3Y)
unnamed: U57.1 (~CLR), U58.6
unnamed: U57.11 (QD), U58.5, U63.11 (C)
unnamed: U57.12 (QC), U58.4
unnamed: U60.11 (QD), U78.10 (3B), U78.14 (4A)
unnamed: U60.15 (RCO), U61.10 (ENT)
unnamed: U62.6, U63.3 (C), U69.10 (B)
unnamed: U63.8 (~Q), U63.12 (D), U64.1 (C), U64.6 (C)
unnamed: U64.9 (J), U64.12 (K), U64.15 (Q)
unnamed: U76.2 (D), U76.6 (~Q)
unnamed: U76.3 (C), U79.11
unnamed: U79.6, U79.9
RS232 IN: J3.3, R66.2
RS232 OUT: J3.2, R65.1
Rx DATA: J3.4, NT2.2, PIN6.1
Rx DATA 1: J3.5, PIN7.1, U63.5 (Q)
Rx DATA 2: J3.6, JP20.1 (A), PIN5.1
T3: U56.13 (2D); also elsewhere on the board
TO R32: R32.2, U59.1 (~CLR), U59.9 (~LOAD), U60.1 (~CLR), U60.9 (~LOAD), U61.1 (~CLR), U61.9 (~LOAD), U63.4 (~S), U63.10 (~S), U63.13 (~R)
TO R86: R86.1, U64.3 (~R), U64.7 (~S), U64.8 (~R), U65.2 (B), U65.3 (1~CLR), U65.10 (B), U65.11 (1~CLR), U69.2 (B), U69.3 (1~CLR), U69.11 (1~CLR)
~32: U76.4 (~S), U78.1 (S); also elsewhere on the board
~BLANK: U56.9 (2A), U69.4 (1~Q); also elsewhere on the board
~HS: U65.12 (2~Q); also elsewhere on the board
~VA: U69.1 (A); also elsewhere on the board
~VS: U65.4 (1~Q); also elsewhere on the board
Φ0 IN: U29.11 (QD), U29.14 (A); also elsewhere on the board

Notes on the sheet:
J3 (4)
J3 (5)
J3 (7)
983.040 kHz
J3 (10)
J3 (2)
Delay
* Signal name does not match 491.52 kHz
J2 (7)
XOR out of phase clocks
* 491.52 kHz, see U29
J75 (5)
J3 (6)
÷16
AUDIO TAPE OUT
J3 (11)
1000pF orig.schem. .001uF ass.instr.
J3 (12)
VSYNC/HSYNC GENERATOR
* Clock doubled crystal f / 64 is 122.88 kHz
VIDEO MODE SELECT
J3 (8)
TAPE INTERFACE
~{VS} 1ms pulse low ~{HS} 10ns pulse low
J2 (9)
AUDIO TAPE IN
Excluded from PCB
J3 (9)
VIDEO COUNTER - 256x256 pixels
J3 (3)
MAIN CLOCK
